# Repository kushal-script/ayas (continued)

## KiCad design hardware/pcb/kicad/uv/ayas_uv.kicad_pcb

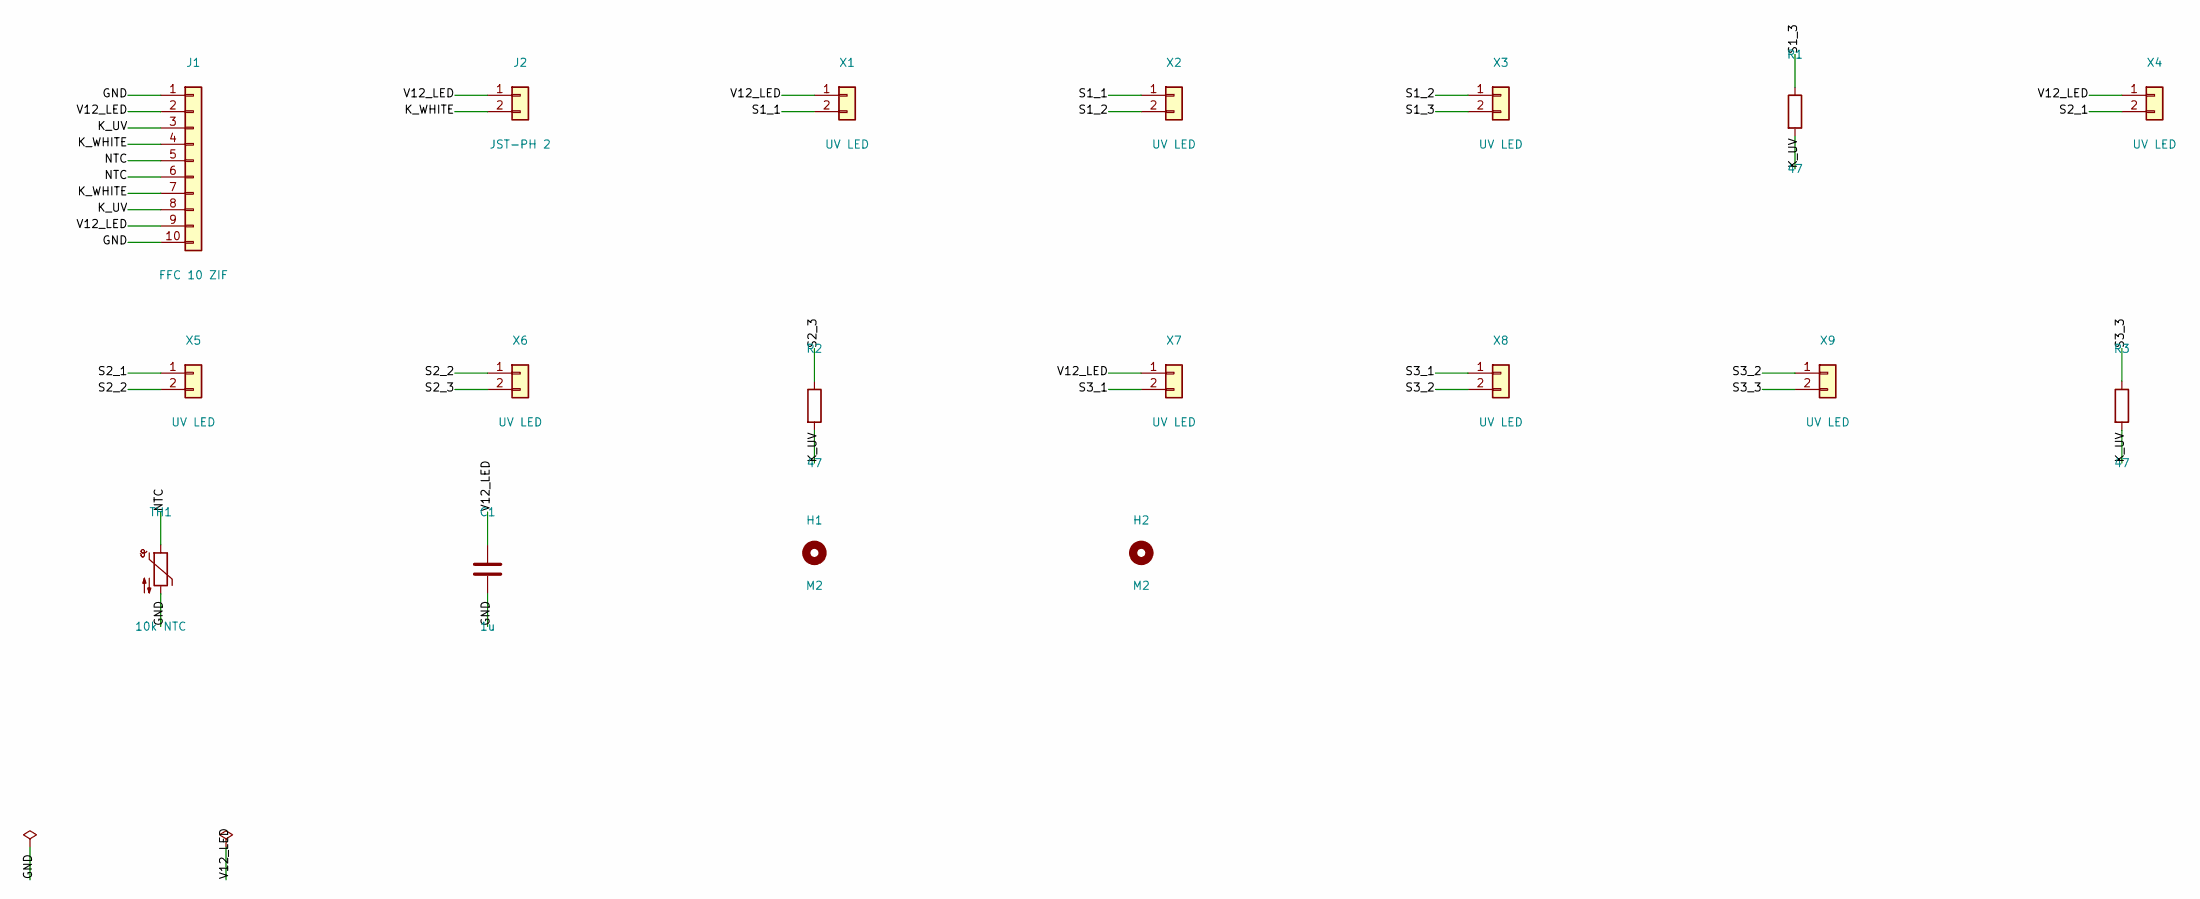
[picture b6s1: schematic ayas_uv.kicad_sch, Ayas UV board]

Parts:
C1: 1u; C_0805_2012Metric; MPN 25 V
H1, H2: M2; MountingHole_2.2mm_M2
J1: FFC 10 ZIF; Molex_200528-0100_1x10-1MP_P1.00mm_Horizontal; MPN 200528-0100 (Molex)
J2: JST-PH 2; JST_PH_B2B-PH-K_1x02_P2.00mm_Vertical; MPN B2B-PH-K-S (JST)
R1, R2, R3: 47; R_0805_2012Metric
TH1: 10k NTC; R_0603_1608Metric; MPN NCP18XH103F03RB (Murata)
X1, X2, X3, X4, X5, X6, X7, X8, X9: UV LED; PinSocket_1x02_P2.54mm_Vertical; MPN 2-pin machined socket, 2.54 mm (Mill-Ma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

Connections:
GND: C1.2, J1.1, J1.10, TH1.2
K_UV: J1.3, J1.8, R1.2, R2.2, R3.2
K_WHITE: J1.4, J1.7, J2.2
NTC: J1.5, J1.6, TH1.1
S1_1: X1.2, X2.1
S1_2: X2.2, X3.1
S1_3: R1.1, X3.2
S2_1: X4.2, X5.1
S2_2: X5.2, X6.1
S2_3: R2.1, X6.2
S3_1: X7.2, X8.1
S3_2: X8.2, X9.1
S3_3: R3.1, X9.2
V12_LED: C1.1, J1.2, J1.9, J2.1, X1.1, X4.1, X7.1

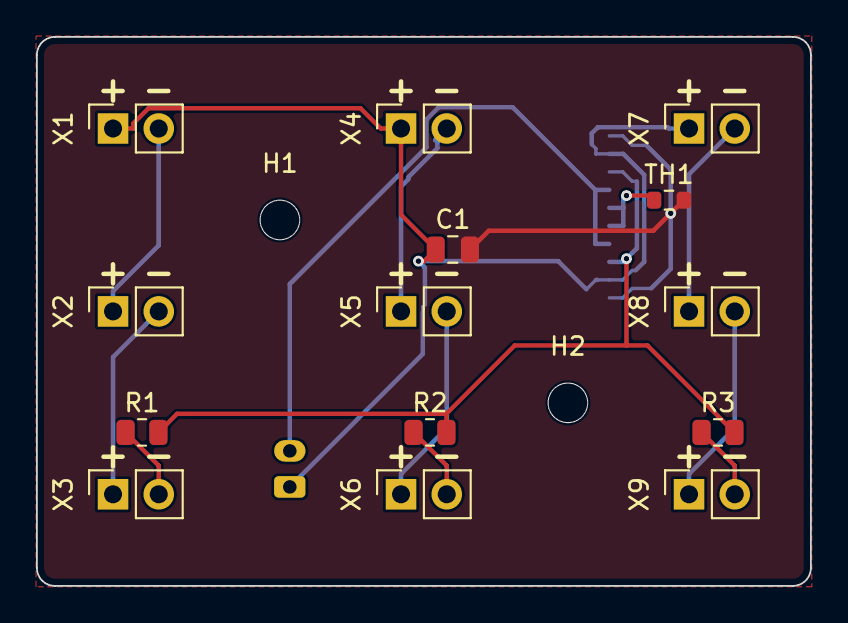
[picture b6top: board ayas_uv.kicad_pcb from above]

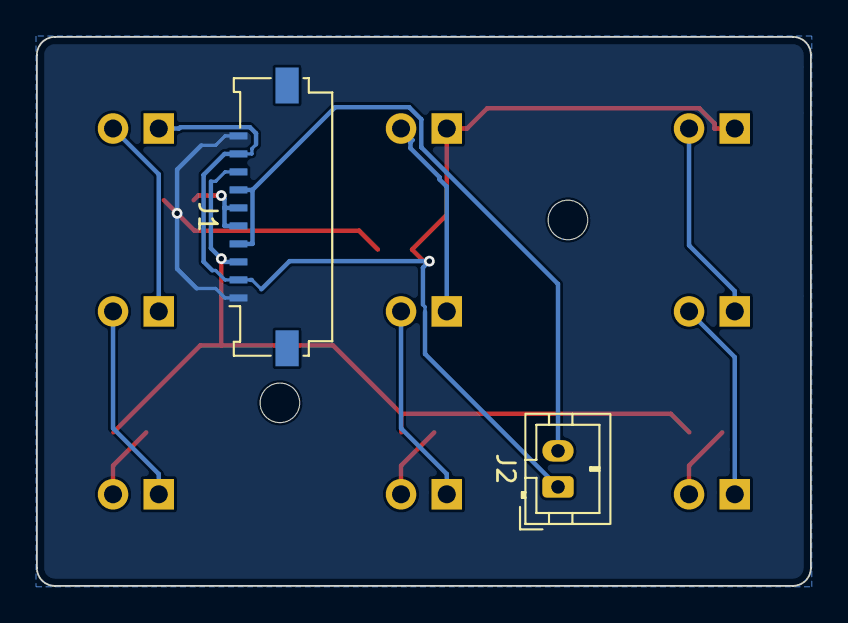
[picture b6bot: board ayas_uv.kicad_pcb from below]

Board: 2 copper layers, 43.0 x 30.5 mm, 18 parts (2 on the bottom side), 14 nets.

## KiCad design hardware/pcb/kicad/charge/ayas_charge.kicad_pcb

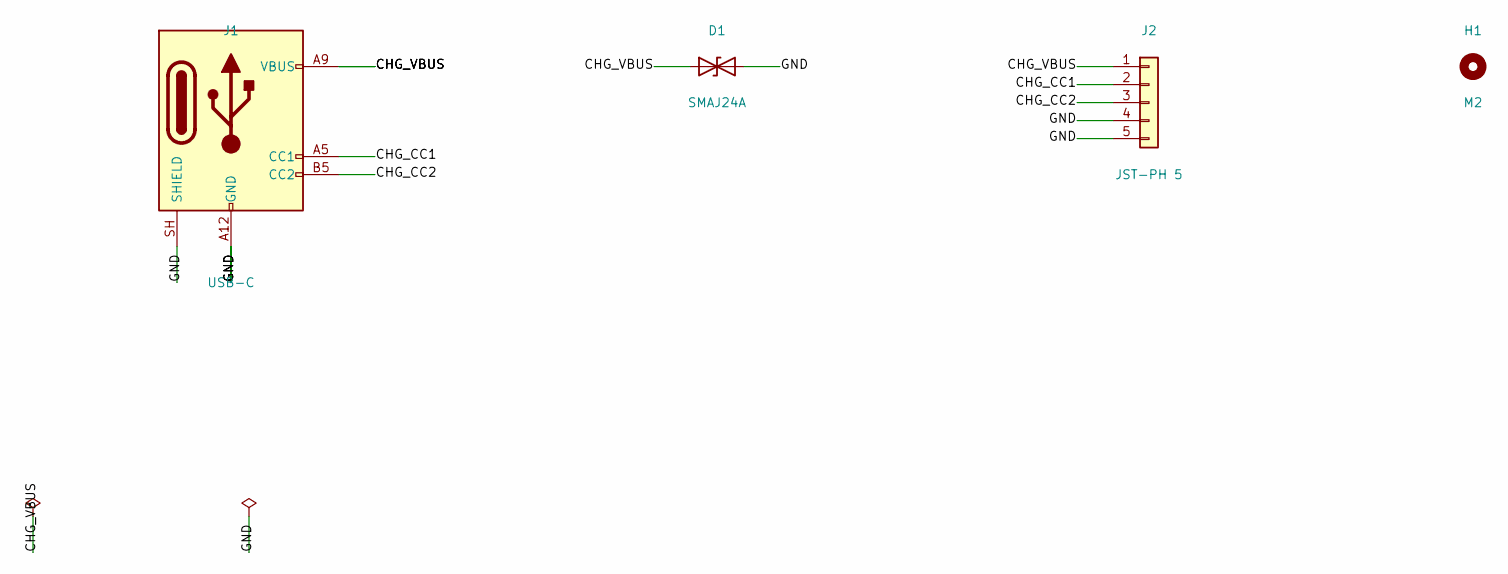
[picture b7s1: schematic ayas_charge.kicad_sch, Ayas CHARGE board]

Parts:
D1: SMAJ24A; D_SMA; MPN SMAJ24A (Littelfuse)
H1: M2; MountingHole_2.2mm_M2
J1: USB-C; USB_C_Receptacle_GCT_USB4125-xx-x_6P_TopMnt_Horizontal; MPN USB4125-GF-A (GCT)
J2: JST-PH 5; JST_PH_B5B-PH-K_1x05_P2.00mm_Vertical; MPN B5B-PH-K-S (JST)

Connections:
CHG_CC1: J1.A5 (CC1), J2.2
CHG_CC2: J1.B5 (CC2), J2.3
CHG_VBUS: D1.1 (A1), J1.A9 (VBUS), J1.B9 (VBUS), J2.1
GND: D1.2 (A2), J1.A12 (GND), J1.B12 (GND), J1.SH (SHIELD), J2.4, J2.5

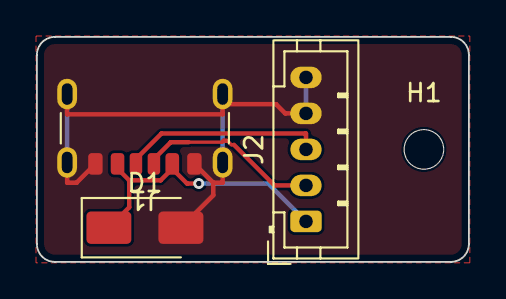
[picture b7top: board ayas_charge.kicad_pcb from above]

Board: 2 copper layers, 24.0 x 12.5 mm, 4 parts (0 on the bottom side), 4 nets.

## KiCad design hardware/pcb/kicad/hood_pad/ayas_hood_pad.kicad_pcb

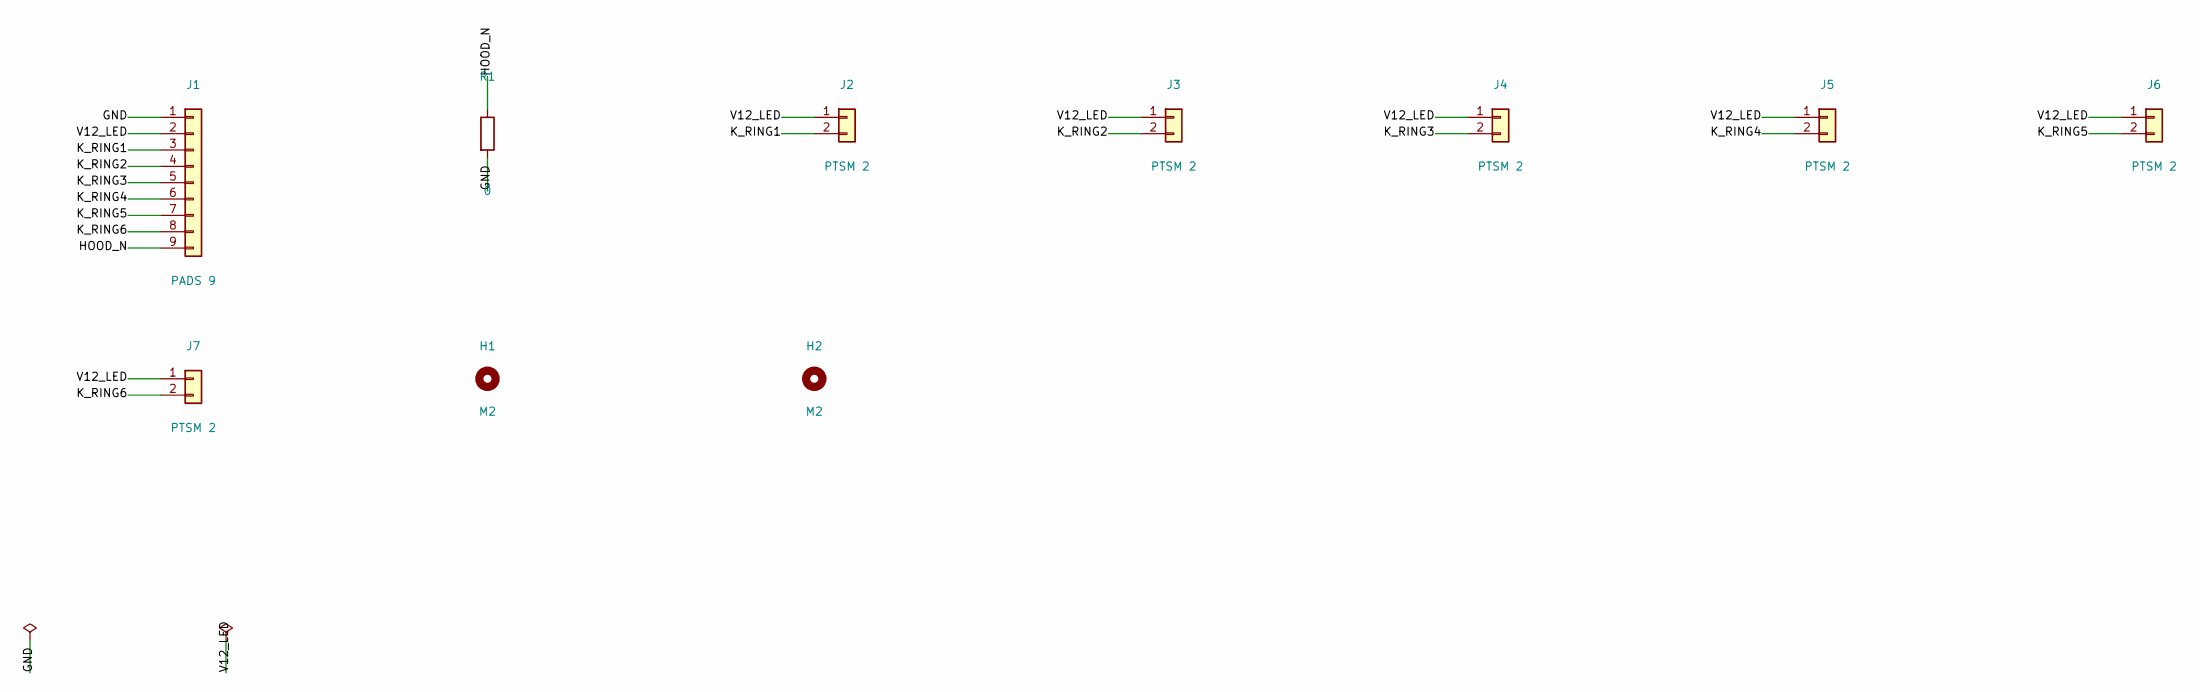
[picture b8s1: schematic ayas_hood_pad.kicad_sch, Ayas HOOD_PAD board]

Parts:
H1, H2: M2; MountingHole_2.2mm_M2
J1: PADS 9; PogoPads_1x09_P2.54mm; MPN ENIG pads
J2, J3, J4, J5, J6, J7: PTSM 2; TerminalBlock_Phoenix_PTSM-0,5-2-2.5-H-THR_1x02_P2.50mm_Hor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; MPN PTSM 0,5/ 2-2,5-H THR (Phoenix Contact)
R1: 0; R_0603_1608Metric

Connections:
GND: J1.1, R1.2
HOOD_N: J1.9, R1.1
K_RING1: J1.3, J2.2
K_RING2: J1.4, J3.2
K_RING3: J1.5, J4.2
K_RING4: J1.6, J5.2
K_RING5: J1.7, J6.2
K_RING6: J1.8, J7.2
V12_LED: J1.2, J2.1, J3.1, J4.1, J5.1, J6.1, J7.1

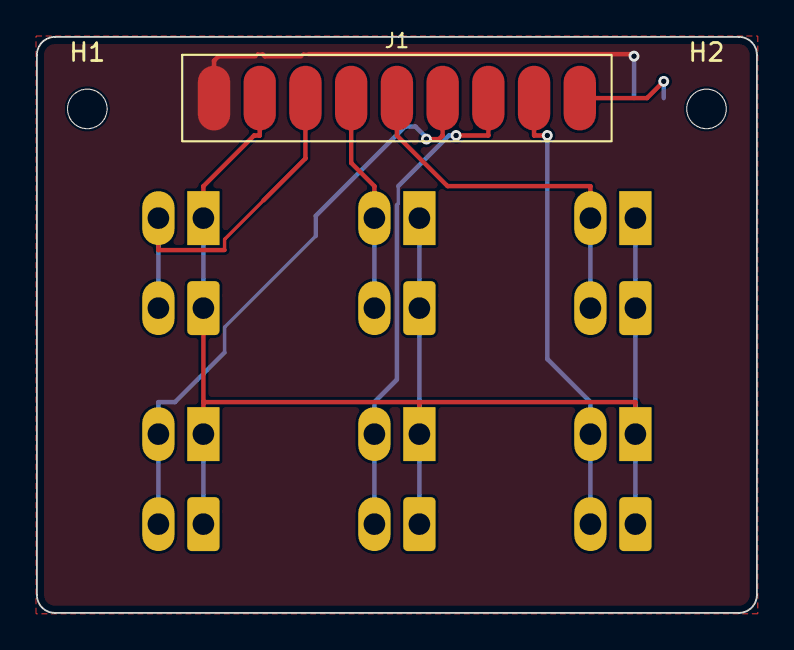
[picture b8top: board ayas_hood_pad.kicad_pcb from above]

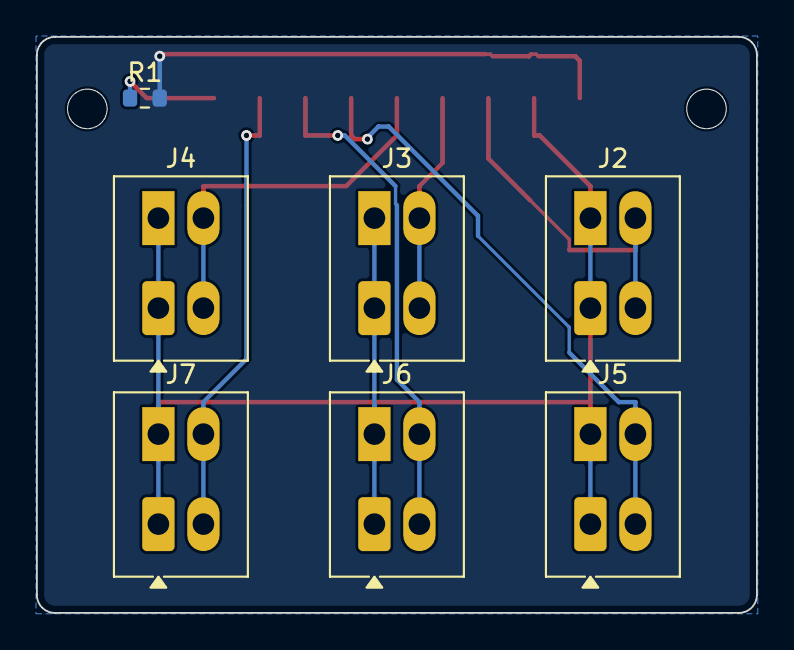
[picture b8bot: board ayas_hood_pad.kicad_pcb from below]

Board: 2 copper layers, 40.0 x 32.0 mm, 10 parts (7 on the bottom side), 9 nets.
